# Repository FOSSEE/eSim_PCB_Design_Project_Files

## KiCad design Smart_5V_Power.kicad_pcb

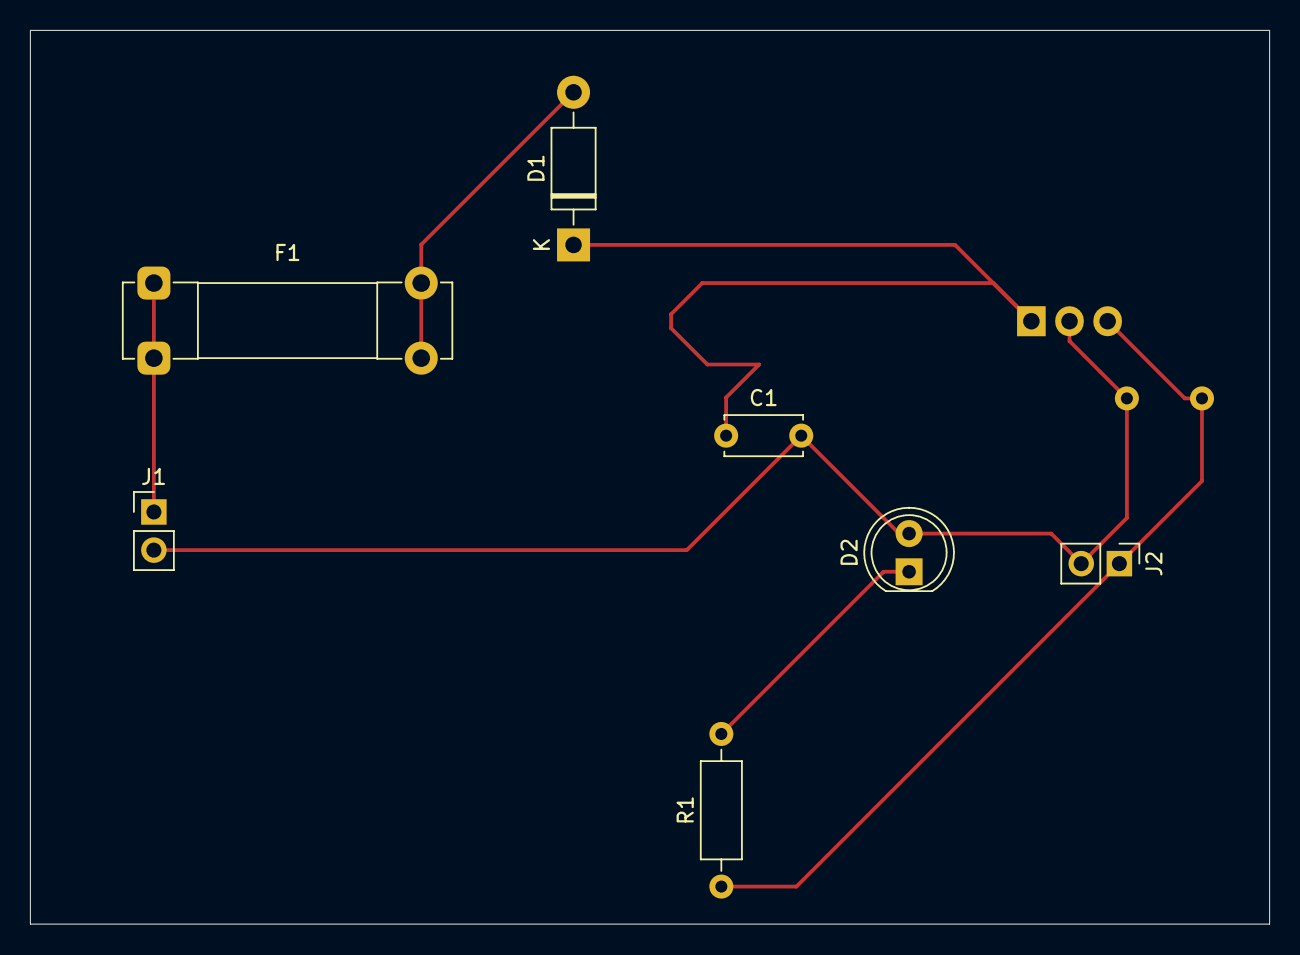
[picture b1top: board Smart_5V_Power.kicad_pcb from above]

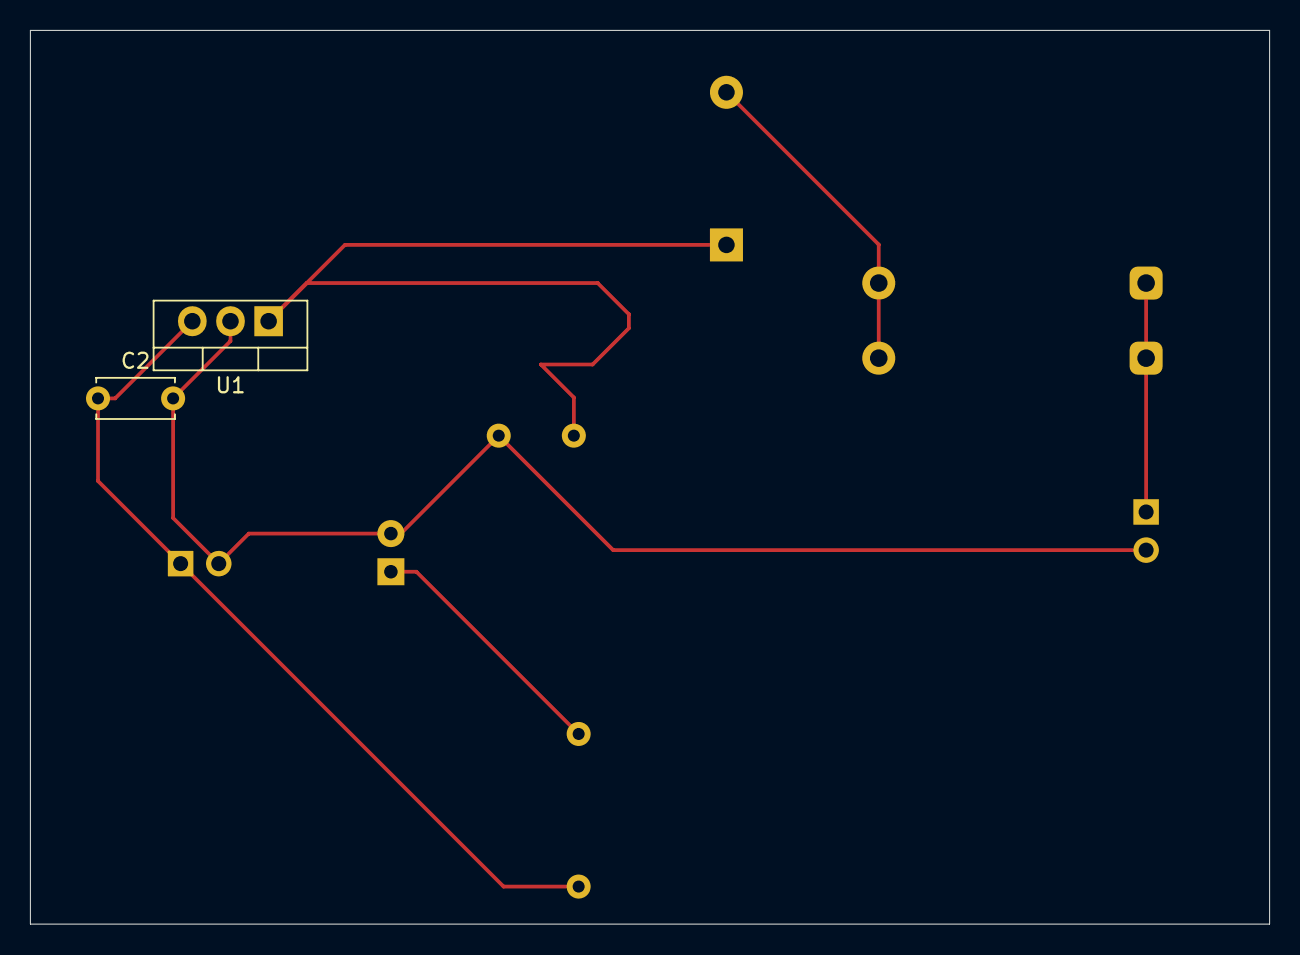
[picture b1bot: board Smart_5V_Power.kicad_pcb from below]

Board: 2 copper layers, 82.5 x 59.5 mm, 9 parts (2 on the bottom side), 6 nets.

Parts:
C1: 0.33uF; C_Disc_D5.0mm_W2.5mm_P5.00mm
C2: 0.1uF; C_Disc_D5.0mm_W2.5mm_P5.00mm
D1: D; D_DO-41_SOD81_P10.16mm_Horizontal
D2: LED; LED_D5.0mm
F1: Fuse; Fuseholder_Clip-5x20mm_Bel_FC-203-22_Lateral_P17.80x5.00mm_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
J1, J2: Conn_01x02; PinHeader_1x02_P2.54mm_Vertical
R1: 1kΩ; R_Axial_DIN0207_L6.3mm_D2.5mm_P10.16mm_Horizontal
U1: L7805; TO-220-3_Vertical

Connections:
GND: C1.2, C2.2, D2.2 (A), J1.2, J2.2, U1.2 (GND)
unnamed: C1.1, D1.1 (K), U1.1 (IN)
unnamed: C2.1, J2.1, R1.1, U1.3 (OUT)
unnamed: D1.2 (A), F1.2
unnamed: D2.1 (K), R1.2
unnamed: F1.1, J1.1

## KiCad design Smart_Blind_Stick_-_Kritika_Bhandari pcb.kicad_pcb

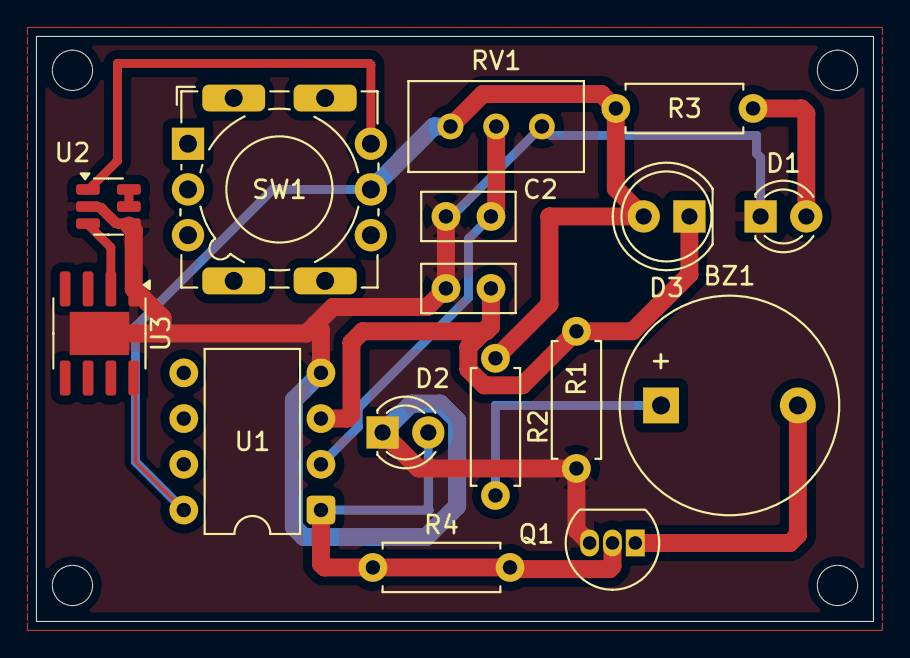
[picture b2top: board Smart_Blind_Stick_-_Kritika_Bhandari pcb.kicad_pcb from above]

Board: 2 copper layers, 46.5 x 32.5 mm, 16 parts (0 on the bottom side), 11 nets.

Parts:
BZ1: Buzzer; Buzzer_12x9.5RM7.6
C1, C2: 10nF; C_Disc_D5.0mm_W2.5mm_P2.50mm
D1, D2: IR204A; LED_D3.0mm_IRBlack
D3: D_Photo; LED_D5.0mm
Q1: BC547; TO-92_Inline
R1, R2: 10k; R_Axial_DIN0207_L6.3mm_D2.5mm_P7.62mm_Horizontal
R3: 220; R_Axial_DIN0207_L6.3mm_D2.5mm_P7.62mm_Horizontal
R4: 1k; R_Axial_DIN0207_L6.3mm_D2.5mm_P7.62mm_Horizontal
RV1: 10k; Potentiometer_Bourns_3296W_Vertical
SW1: SW_SP3T_NR01103; SW_NKK_NR01
U1: LM4250; DIP-8_W7.62mm
U2: TP4057; TSOT-23-6
U3: LGS5500EP; SOIC-8-1EP_3.9x4.9mm_P1.27mm_EP2.41x3.3mm

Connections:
GND: C1.1, C2.1, D1.1 (K), D2.1 (K), Q1.3 (E), R1.2, RV1.1, U1.4 (V-), U2.2 (GND), U2.4 (V_{CC}), U3.1 (ISET), U3.9 (GND)
unnamed: BZ1.1 (+), R2.2
unnamed: BZ1.2 (-), Q1.1 (C)
unnamed: D1.2 (A), R3.1
unnamed: D2.2 (A), Q1.2 (B), R4.1, R4.2, U1.1 (NULL)
unnamed: C1.2, D3.1 (K), R1.1, U1.3 (+)
unnamed: C2.2, RV1.2, U1.2 (-)
unnamed: U2.3 (BAT), U3.2 (VIN)
unnamed: SW1.2, U2.1 (~CHRG)
VCC: D3.2 (A), R2.1, R3.2, RV1.3, SW1.3, U1.8 (IQ), U3.8 (NTC)
out: U2.5 (STDBY), U2.6 (PROG)

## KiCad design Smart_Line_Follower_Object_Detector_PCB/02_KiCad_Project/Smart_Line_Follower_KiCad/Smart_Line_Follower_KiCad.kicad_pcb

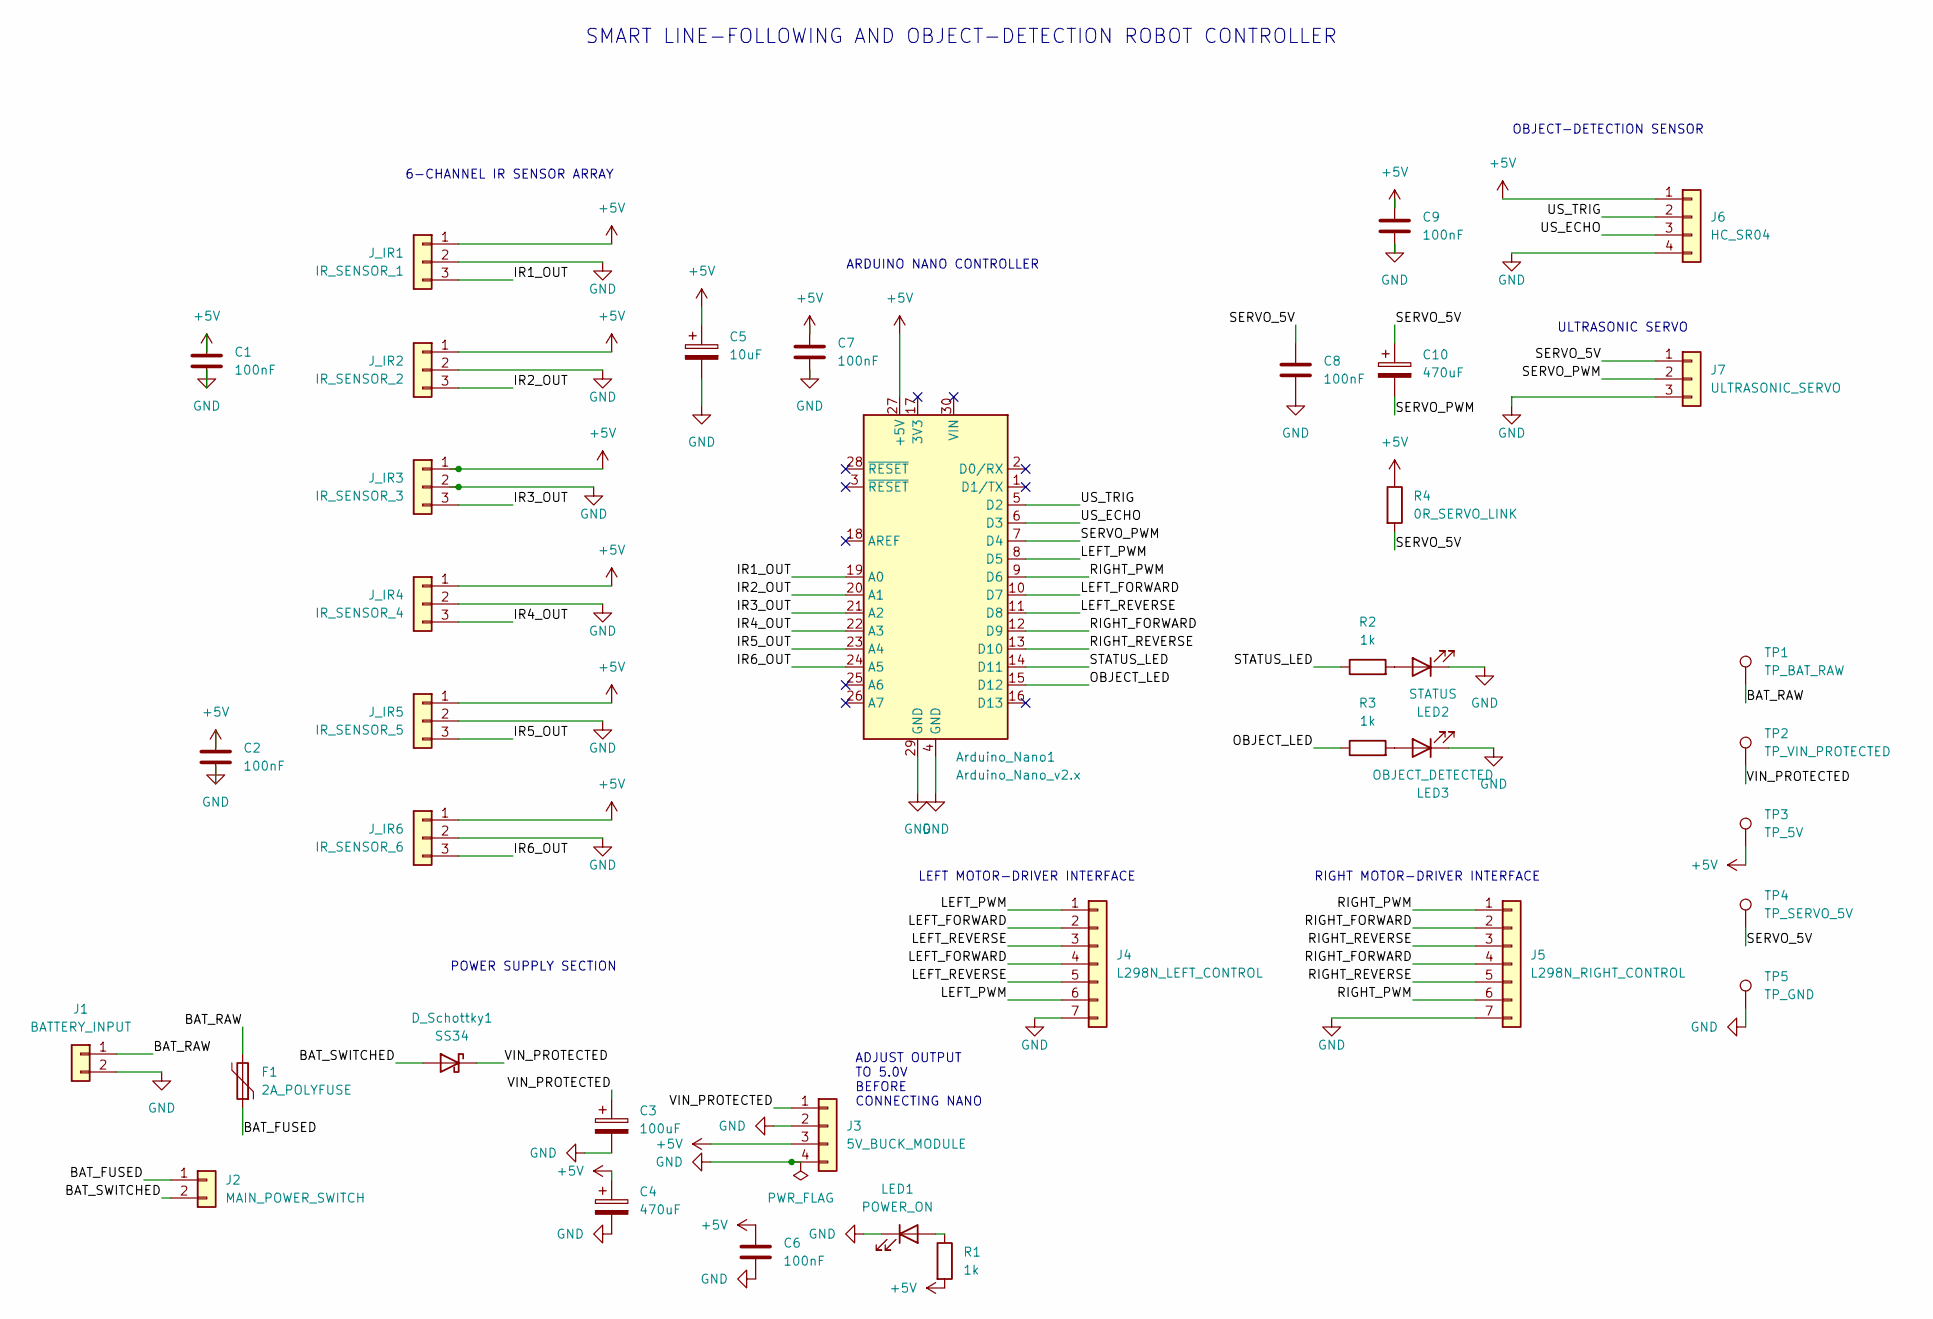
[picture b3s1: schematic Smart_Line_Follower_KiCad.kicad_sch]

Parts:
Arduino_Nano1: Arduino_Nano_v2.x; Arduino_Nano
C1, C2, C6, C7, C8, C9: 100nF; C_Disc_D5.0mm_W2.5mm_P5.00mm
C3: 100uF; CP_Radial_D6.3mm_P2.50mm
C4, C10: 470uF; CP_Radial_D10.0mm_P5.00mm
C5: 10uF; CP_Radial_D5.0mm_P2.00mm
D_Schottky1: SS34; D_SMA
F1: 2A_POLYFUSE; Fuse_Bourns_MF-RG300
J1: BATTERY_INPUT; TerminalBlock_bornier-2_P5.08mm
J2: MAIN_POWER_SWITCH; PinHeader_1x02_P2.54mm_Vertical
J3: 5V_BUCK_MODULE; PinHeader_1x04_P2.54mm_Vertical
J4: L298N_LEFT_CONTROL; PinHeader_1x07_P2.54mm_Vertical
J5: L298N_RIGHT_CONTROL; PinHeader_1x07_P2.54mm_Vertical
J6: HC_SR04; PinHeader_1x04_P2.54mm_Vertical
J7: ULTRASONIC_SERVO; PinHeader_1x03_P2.54mm_Vertical
J_IR1: IR_SENSOR_1; PinHeader_1x03_P2.54mm_Vertical
J_IR2: IR_SENSOR_2; PinHeader_1x03_P2.54mm_Vertical
J_IR3: IR_SENSOR_3; PinHeader_1x03_P2.54mm_Vertical
J_IR4: IR_SENSOR_4; PinHeader_1x03_P2.54mm_Vertical
J_IR5: IR_SENSOR_5; PinHeader_1x03_P2.54mm_Vertical
J_IR6: IR_SENSOR_6; PinHeader_1x03_P2.54mm_Vertical
LED1: POWER_ON; LED_D5.0mm
LED2: STATUS; LED_D5.0mm
LED3: OBJECT_DETECTED; LED_D5.0mm
R1, R2, R3: 1k; R_Axial_DIN0207_L6.3mm_D2.5mm_P10.16mm_Horizontal
R4: 0R_SERVO_LINK; R_Axial_DIN0207_L6.3mm_D2.5mm_P10.16mm_Horizontal
TP1: TP_BAT_RAW; TestPoint_THTPad_D2.0mm_Drill1.0mm
TP2: TP_VIN_PROTECTED; TestPoint_THTPad_D2.0mm_Drill1.0mm
TP3: TP_5V; TestPoint_THTPad_D2.0mm_Drill1.0mm
TP4: TP_SERVO_5V; TestPoint_THTPad_D2.0mm_Drill1.0mm
TP5: TP_GND; TestPoint_THTPad_D2.0mm_Drill1.0mm

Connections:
+5V: Arduino_Nano1.27 (+5V), C1.1, C2.1, C4.1, C5.1, C6.1, C7.1, C9.1, J3.3, J6.1, J_IR1.1, J_IR2.1, J_IR3.1, J_IR4.1, J_IR5.1, J_IR6.1, R1.2, R4.1, TP3.1
/BAT_FUSED: F1.1, J2.1
/BAT_RAW: F1.2, J1.1, TP1.1
/BAT_SWITCHED: D_Schottky1.2 (A), J2.2
/IR1_OUT: Arduino_Nano1.19 (A0), J_IR1.3
/IR2_OUT: Arduino_Nano1.20 (A1), J_IR2.3
/IR3_OUT: Arduino_Nano1.21 (A2), J_IR3.3
/IR4_OUT: Arduino_Nano1.22 (A3), J_IR4.3
/IR5_OUT: Arduino_Nano1.23 (A4), J_IR5.3
/IR6_OUT: Arduino_Nano1.24 (A5), J_IR6.3
/LEFT_FORWARD: Arduino_Nano1.10 (D7), J4.2, J4.4
/LEFT_PWM: Arduino_Nano1.8 (D5), J4.1, J4.6
/LEFT_REVERSE: Arduino_Nano1.11 (D8), J4.3, J4.5
/OBJECT_LED: Arduino_Nano1.15 (D12), R3.1
/RIGHT_FORWARD: Arduino_Nano1.12 (D9), J5.2, J5.4
/RIGHT_PWM: Arduino_Nano1.9 (D6), J5.1, J5.6
/RIGHT_REVERSE: Arduino_Nano1.13 (D10), J5.3, J5.5
/SERVO_5V: C8.1, C10.1, J7.1, R4.2, TP4.1
/SERVO_PWM: Arduino_Nano1.7 (D4), C10.2, J7.2
/STATUS_LED: Arduino_Nano1.14 (D11), R2.1
/US_ECHO: Arduino_Nano1.6 (D3), J6.3
/US_TRIG: Arduino_Nano1.5 (D2), J6.2
/VIN_PROTECTED: C3.1, D_Schottky1.1 (K), J3.1, TP2.1
GND: Arduino_Nano1.4 (GND), Arduino_Nano1.29 (GND), C1.2, C2.2, C3.2, C4.2, C5.2, C6.2, C7.2, C8.2, C9.2, J1.2, J3.2, J3.4, J4.7, J5.7, J6.4, J7.3, J_IR1.2, J_IR2.2, J_IR3.2, J_IR4.2, J_IR5.2, J_IR6.2, LED1.1 (K), LED2.1 (K), LED3.1 (K), TP5.1
unnamed: LED1.2 (A), R1.1
unnamed: LED2.2 (A), R2.2
unnamed: LED3.2 (A), R3.2

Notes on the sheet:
ARDUINO NANO CONTROLLER
LEFT MOTOR-DRIVER INTERFACE
ULTRASONIC SERVO
ADJUST OUTPUT TO 5.0V BEFORE CONNECTING NANO
6-CHANNEL IR SENSOR ARRAY
RIGHT MOTOR-DRIVER INTERFACE
OBJECT-DETECTION SENSOR
SMART LINE-FOLLOWING AND OBJECT-DETECTION ROBOT CONTROLLER
POWER SUPPLY SECTION

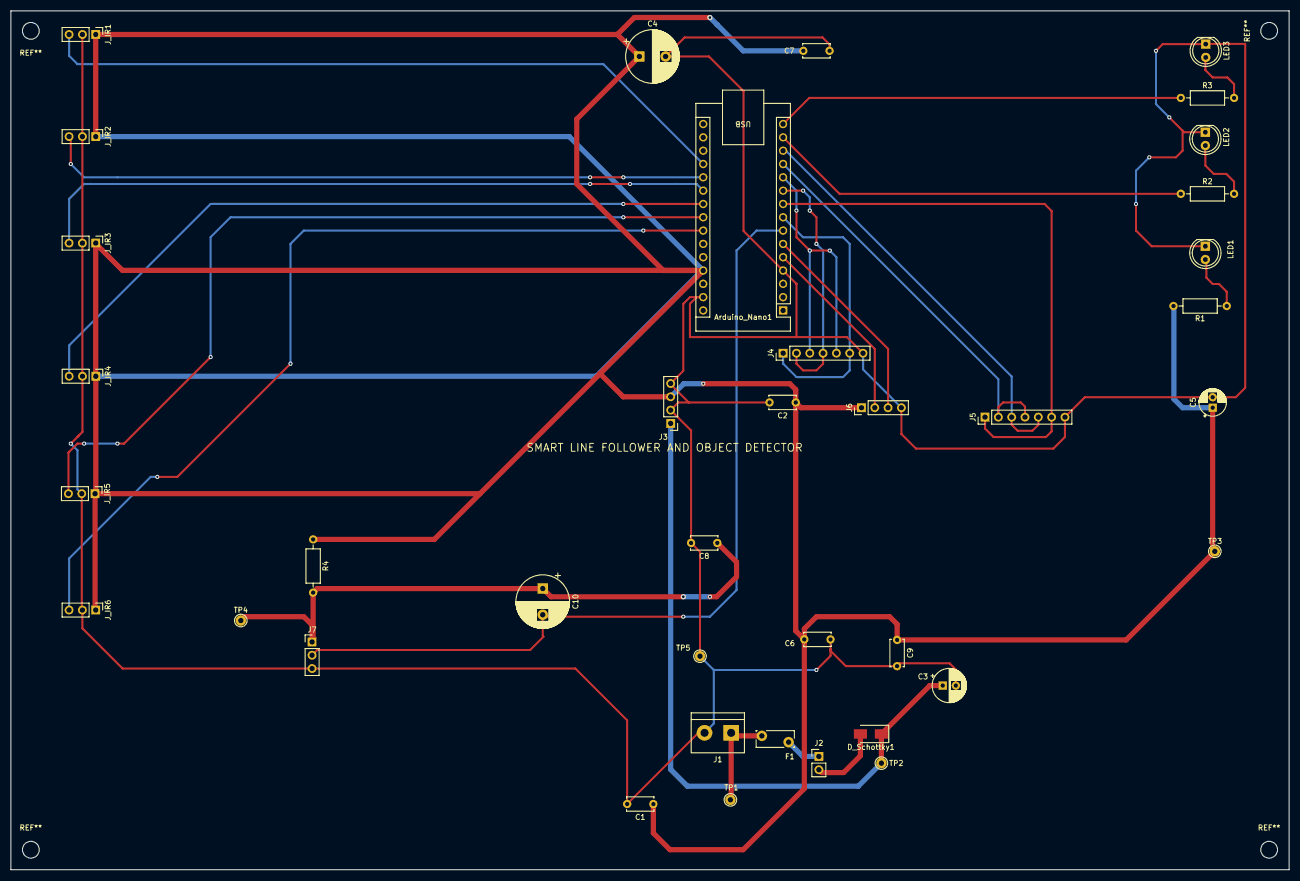
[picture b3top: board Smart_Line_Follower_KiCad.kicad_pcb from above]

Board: 2 copper layers, 243.8 x 163.8 mm, 38 parts (0 on the bottom side), 27 nets.

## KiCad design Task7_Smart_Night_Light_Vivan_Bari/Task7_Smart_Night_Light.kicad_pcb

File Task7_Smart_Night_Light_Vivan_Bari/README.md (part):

# Smart Automatic Night Light Controller Using eSim

### FOSSEE Winter Internship 2026 | Screening Task 7 — PCB Design

Developed by: Vivan Bari  
Domain: Electronics and Communication Engineering  
Software: eSim 2.6, KiCad 9.0.3  
Project Type: Two-Layer PCB Design  
Power Supply: 5V DC

---

## 1. Project Overview

This project presents the schematic design and two-layer PCB layout of a Smart Automatic Night Light Controller using eSim.

The circuit is designed to detect changes in ambient light intensity and automatically control an LED. It uses a Light Dependent Resistor (LDR) as the sensing element, an LM393 comparator for threshold detection, and a 2N7000 N-channel MOSFET for LED switching.

A 10 kΩ potentiometer provides an adjustable reference voltage, allowing the switching threshold to be changed according to the required lighting conditions.

The project was developed as part of Screening Task 7 for the FOSSEE Winter Internship 2026.

The main focus was to complete the PCB design workflow, from schematic capture and footprint assignment to routing, design-rule verification, and 3D visualization.

## 2. Project Objectives

The objectives of this project were to:

1. Design a light-sensitive switching circuit using analog electronic components.
2. Implement the circuit schematic using eSim.
3. Select suitable component footprints for PCB implementation.
4. Design a two-layer PCB using KiCad.
5. Route the required electrical connections while maintaining appropriate clearances.
6. Implement a copper ground plane.
7. Verify the schematic and PCB using ERC and DRC.
8. Generate a 3D representation of the completed PCB.

## 3. Working Principle

The proposed circuit operates by comparing a light-dependent voltage with an adjustable reference voltage.

### 3.1 Light Detection

The light-sensing section consists of an LDR (R1) and a fixed 10 kΩ resistor (R2).

These components form a voltage divider connected between the 5V supply and ground.

The output voltage of this divider depends on the resistance of the LDR.

The sensor voltage is given by:

**V_sensor = 5 × R_LDR / (10,000 + R_LDR)**

where R_LDR represents the instantaneous resistance of the LDR in ohms.

When ambient light intensity increases, the LDR resistance decreases, causing the sensor voltage to fall.

When the surroundings become darker, the LDR resistance increases, causing the sensor voltage to rise.

### 3.2 Voltage Comparison

The LM393 comparator compares the sensor voltage with the reference voltage generated by the 10 kΩ potentiometer (RV1).

The connections are:

- Non-inverting input (+): LDR voltage divider output.
- Inverting input (−): Adjustable potentiometer output.
- Comparator output: MOSFET gate-control circuit.

The LM393 has an open-collector output, so a 10 kΩ pull-up resistor (R4) is connected to the 5V supply.

When the sensor voltage exceeds the reference voltage, the comparator output transistor is switched off, allowing the output voltage to rise through R4.

When the sensor voltage falls below the reference, the comparator pulls its output low.

### 3.3 LED Switching

A 2N7000 N-channel MOSFET acts as the switching device.

Its gate is connected to the LM393 output. The drain is connected to the LED cathode, while the source is connected to ground.

A 330 Ω resistor (R3) limits the LED current.

The intended switching behavior is:

| Lighting condition | Sensor voltage | Comparator output | LED |
|---|---|---|---|
| Bright surroundings | Below reference | LOW | OFF |
| Dark surroundings | Above reference | HIGH through pull-up | ON |

This table describes the intended operation based on the circuit topology. Functional simulation and physical testing have not yet been performed.

## 4. Components Used

The circuit uses the following components:

| Reference | Component | Value / Model | Purpose |
|---|---|---|---|
| U1 | Dual comparator | LM393 | Light-threshold detection |
| R1 | Light Dependent Resistor | R_Photo | Ambient light sensing |
| R2 | Fixed resistor | 10 kΩ | Sensor voltage divider |
| R3 | Fixed resistor | 330 Ω | LED current limiting |
| R4 | Fixed resistor | 10 kΩ | Comparator output pull-up |
| R5 | Fixed resistor | 10 kΩ | Unused comparator bias network |
| R6 | Fixed resistor | 10 kΩ | Unused comparator bias network |
| RV1 | Potentiometer | 10 kΩ | Adjustable threshold |
| Q1 | N-channel MOSFET | 2N7000 | LED switching |
| D1 | LED | LED | Light output |
| C1 | Ceramic capacitor | 100 nF | Supply decoupling |
| J1 | Two-pin connector | 5V input | External power connection |

The LM393 contains two comparators. One comparator is used for light detection, while the second is connected to a defined bias network to avoid floating inputs.

## 5. Schematic Design

The circuit schematic was created using the KiCad Schematic Editor integrated with eSim.

The design was divided into four functional sections:

**Power Supply:** A two-pin connector supplies 5V and GND to the circuit. A 100 nF ceramic capacitor is connected across the supply for decoupling.

**Sensor Circuit:** The LDR and a 10 kΩ fixed resistor form a voltage divider that produces a light-dependent signal.

**Comparator Circuit:** The LM393 compares the sensor voltage against the adjustable reference voltage. A pull-up resistor provides the HIGH output state.

**Output Circuit:** The 2N7000 MOSFET controls current through the LED and its series resistor.

After completing the schematic connections, the Electrical Rules Checker was used to identify and resolve electrical-rule violations.

The final ERC run reported zero errors and zero warnings.

## 6. PCB Design and Layout

The PCB was designed using KiCad 9.0.3 through the eSim 2.6 workflow.

### 6.1 Footprint Assignment

Through-hole footprints were selected for the components.

The major footprints include:

| Component | Footprint |
|---|---|
| LM393 | DIP-8, 7.62 mm width |
| Fixed resistors | DIN0207 axial resistor |
| Ceramic capacitor | 5 mm disc capacitor |
| LED | 5 mm through-hole LED |
| 2N7000 | TO-92 Inline |
| LDR | Vertical LDR footprint |
| Potentiometer | Bourns 3296W Vertical |
| Power connector | Phoenix 2-pin, 5 mm pitch |

The footprint assignments were checked against the schematic pin numbers. Physical compatibility with the exact purchased parts should be confirmed before fabrication.

### 6.2 Component Placement

The components were arranged according to their functions and electrical connections.

The power connector was positioned toward one side of the PCB, followed by the sensor network and comparator.

The LED and MOSFET were placed toward the output side, while the potentiometer was positioned where its adjustment screw could be accessed.

The decoupling capacitor was placed near the LM393.

The layout was organized to reduce unnecessary routing distances while keeping sufficient spacing between component footprints.

### 6.3 PCB Routing

The PCB uses two copper layers:

- **F.Cu:** Front copper layer.
- **B.Cu:** Back copper layer.

A nominal signal track width of 0.30 mm was configured during layout.

Most signal and supply connections were routed on the front copper layer.

The back copper layer was used where necessary to complete connections that could not be routed conveniently on the front.

The routing was performed using KiCad's interactive routing tools, which helped maintain the configured electrical clearances.

### 6.4 Ground Plane

A copper-filled zone connected to the GND net was added on the back copper layer.

The ground plane provides a common ground connection for the circuit components and reduces the need for individual ground traces.

Thermal relief connections were used for through-hole pads where applicable.

The copper zone was refilled before running the final PCB verification.

## 7. Design Verification

The design was checked using KiCad's Electrical Rules Checker and Design Rules Checker.

### 7.1 Electrical Rules Check

The schematic was checked for electrical connection problems and incompatible pin connections.

**Final ERC result:**

| Parameter | Result |
|---|---|
| Errors | 0 |
| Warnings | 0 |

### 7.2 Design Rules Check

The completed PCB was checked for routing violations, disconnected electrical nets, and schematic-to-PCB consistency.

**Final DRC result:**

| Parameter | Result |
|---|---|
| Design-rule violations | 0 |
| Unconnected items | 0 |
| Schematic parity errors | 0 |
| Reported errors | 0 |
| Reported warnings | 0 |

The verification was performed using the configured KiCad design rules.

Five tests were listed as ignored in the DRC window. Therefore, these results should not be interpreted as a complete manufacturing certification.

### 7.3 3D Visualization

The completed PCB was examined using the KiCad 3D Viewer.

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
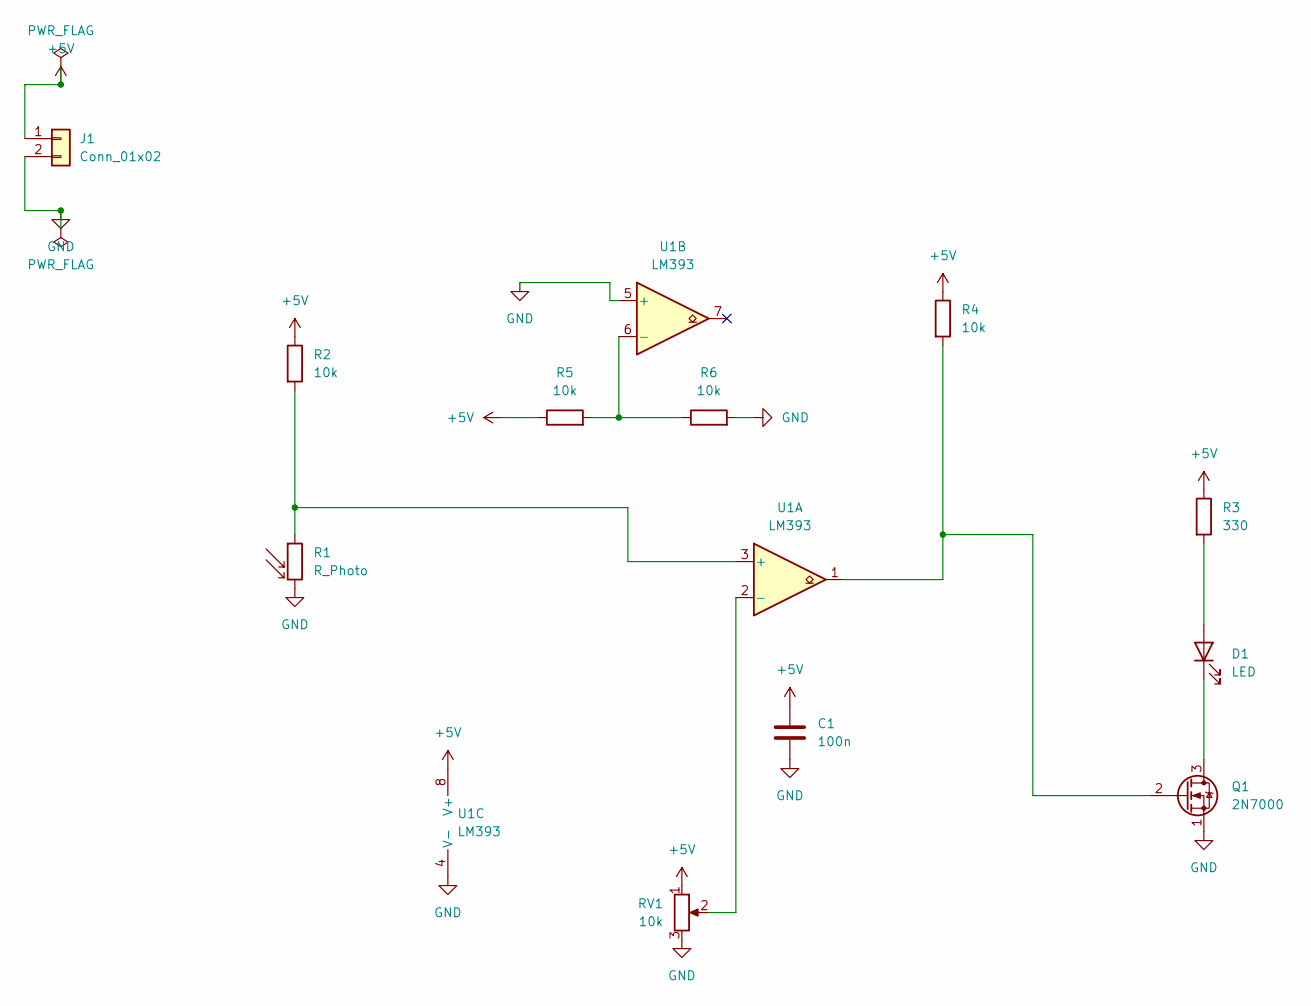
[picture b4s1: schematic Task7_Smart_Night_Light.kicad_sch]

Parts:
C1: 100n; C_Disc_D5.0mm_W2.5mm_P5.00mm
D1: LED; LED_D5.0mm
J1: Conn_01x02; TerminalBlock_Phoenix_MKDS-1,5-2_1x02_P5.00mm_Horizontal
Q1: 2N7000; TO-92_Inline
R1: R_Photo; R_LDR_5.1x4.3mm_P3.4mm_Vertical
R2, R4, R5, R6: 10k; R_Axial_DIN0207_L6.3mm_D2.5mm_P7.62mm_Horizontal
R3: 330; R_Axial_DIN0207_L6.3mm_D2.5mm_P7.62mm_Horizontal
RV1: 10k; Potentiometer_Bourns_3296W_Vertical
U1: LM393; DIP-8_W7.62mm

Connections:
+5V: C1.1, J1.1, R2.1, R3.1, R4.1, R5.1, RV1.1, U1.8 (V+)
GND: C1.2, J1.2, Q1.1 (S), R1.2, R6.2, RV1.3, U1.4 (V-), U1.5 (+)
unnamed: D1.2 (A), R3.2
unnamed: D1.1 (K), Q1.3 (D)
unnamed: Q1.2 (G), R4.2, U1.1
unnamed: R1.1, R2.2, U1.3 (+)
unnamed: RV1.2, U1.2 (-)
unnamed: R5.2, R6.1, U1.6 (-)

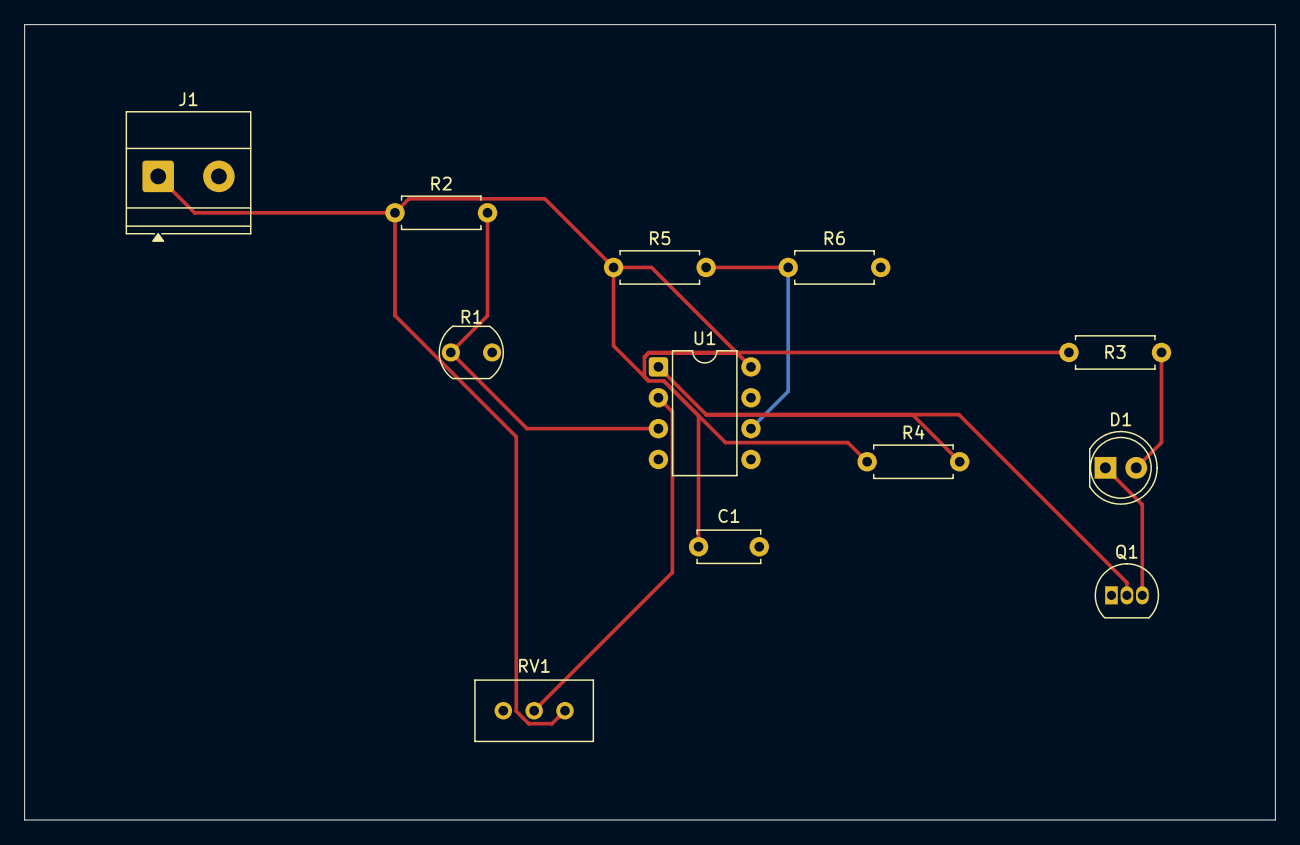
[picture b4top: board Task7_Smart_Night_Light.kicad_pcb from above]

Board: 2 copper layers, 103.0 x 65.5 mm, 12 parts (0 on the bottom side), 8 nets.

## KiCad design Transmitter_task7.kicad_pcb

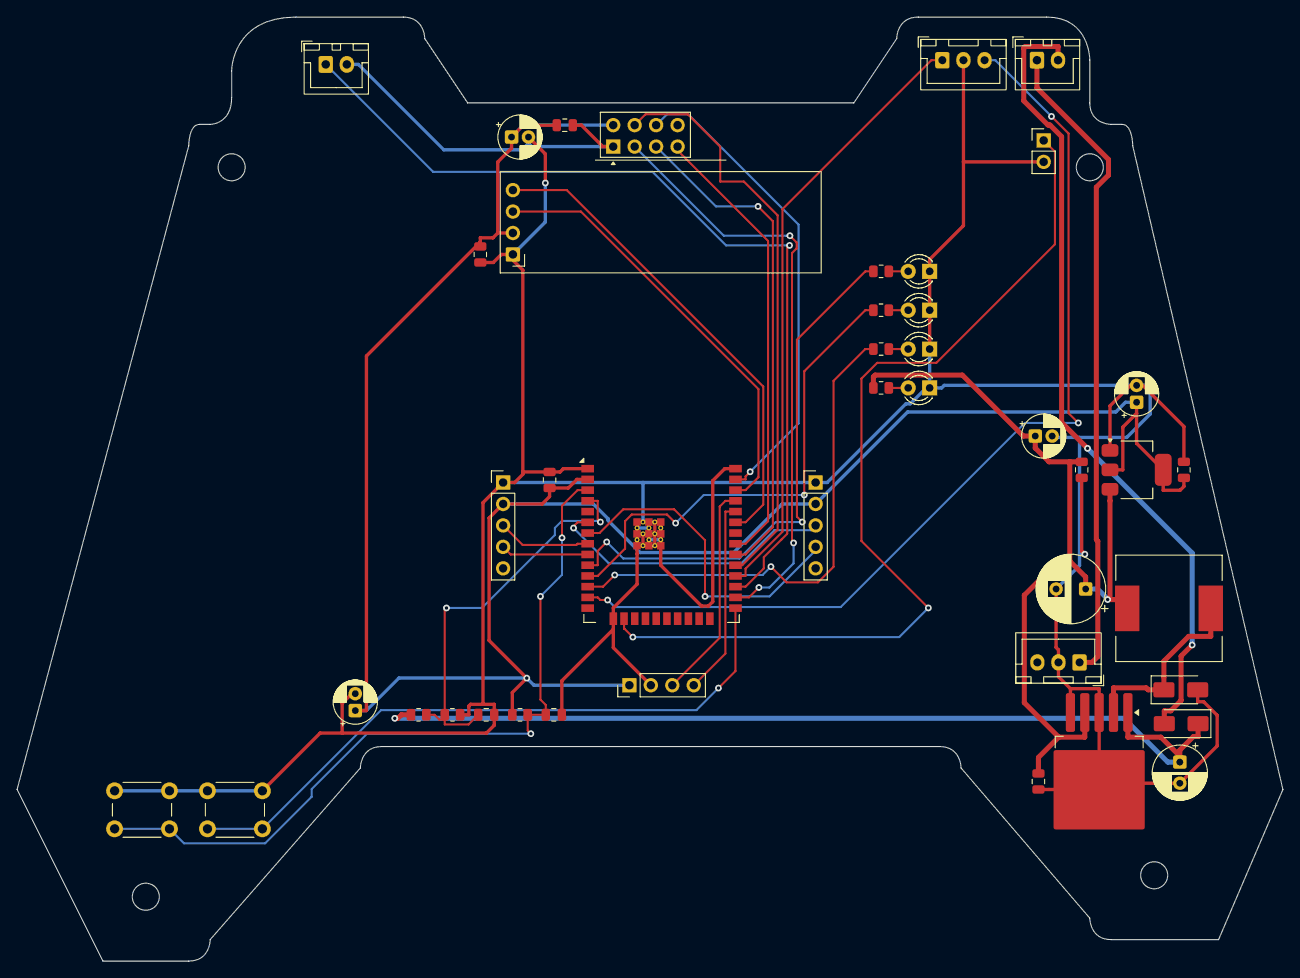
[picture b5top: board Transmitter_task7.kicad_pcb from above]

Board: 2 copper layers, 149.9 x 111.8 mm, 47 parts (0 on the bottom side), 34 nets.

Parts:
C2: 100uF; CP_Radial_D6.3mm_P2.50mm
C3: 220uF; CP_Radial_D8.0mm_P3.50mm
C4, C6, C8, C10, C14, C15: 0.1uF; C_0805_2012Metric
C5, C7, C9, C13: 10uF; CP_Radial_D5.0mm_P2.00mm
C11, C12: 1uF; C_0805_2012Metric
D1, D4, D5, D6: LED; LED_D3.0mm
D2: D_Schottky; D_SMA
D3: SS34; D_SMA
H1, H2, H3, H4: MountingHole; MountingHole_3.2mm_M3
J1: Conn_01x04_Socket; PinHeader_1x04_P2.54mm_Vertical
J2: Conn_01x02_Pin; PinHeader_1x02_P2.54mm_Vertical
J3, J9: Conn_01x05_Socket; PinHeader_1x05_P2.54mm_Vertical
J4: Conn_01x02_Pin; JST_XH_B3B-XH-A_1x03_P2.50mm_Vertical
L1: 33uH; L_12x12mm_H8mm
R1, R2: 10k; R_0805_2012Metric
R3: 20k; R_0805_2012Metric
R4, R5, R6: 330; R_0805_2012Metric
R7: 470; R_0805_2012Metric
SW1, SW3: SW_SPST; JST_XH_B2B-XH-A_1x02_P2.50mm_Vertical
SW2: SW_SPDT; JST_XH_B3B-XH-A_1x03_P2.50mm_Vertical
SW_BOOT1: SW_Push; SW_PUSH_6mm
SW_RST1: SW_Push; SW_PUSH_6mm
U1: NRF24L01_Breakout; nRF24L01_Breakout
U2: ESP32-WROOM-32E
U3: ER_OLEDM0.91_1x-I2C
U5: AMS1117-3.3; SOT-223-3_TabPin2
U6: LM2596S-5; TO-263-5_TabPin3

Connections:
+3V3: C7.1, C8.1, C9.1, C10.1, C13.1, C14.1, C15.1, J1.1, J3.2, J9.2, R1.1, U1.2 (VCC), U2.2 (VDD), U3.2 (VCC), U5.2 (VO)
+5V: C3.1, C4.1, C5.1, C6.1, L1.1, R7.1, U5.3 (VI), U6.4 (FB)
+BATT: C2.1, D2.1 (K), R3.1, U6.1 (VIN)
BATT_SENSE: C12.1, R2.1, R3.2, U2.4 (SENSOR_VP)
BUZZER: J2.1, U2.16 (IO13)
GND: C2.2, C3.2, C4.2, C5.2, C6.2, C7.2, C8.2, C9.2, C10.2, C11.2, C12.2, C13.2, C14.2, C15.2, D1.1 (K), D3.2 (A), D4.1 (K), D5.1 (K), D6.1 (K), J1.2, J2.2, J3.1, J4.2, J9.1, R2.2, SW2.2 (B), SW3.2 (B), SW_BOOT1.1, SW_RST1.1, U1.1 (GND), U2.1 (GND), U2.15 (GND), U2.38 (GND), U2.39 (GND), U3.1 (GND), U5.1 (GND), U6.3 (GND), U6.5 (~ON/OFF)
JOY1_X: J3.3, U2.8 (IO32)
JOY1_Y: J3.4, U2.9 (IO33)
JOY2_X: J9.3, U2.6 (IO34)
JOY2_Y: J9.4, U2.7 (IO35)
LED_ARM: R4.1, U2.10 (IO25)
LED_LINK: R6.1, U2.12 (IO27)
LED_MODE: R5.1, U2.11 (IO26)
NRF_CE: U1.3 (CE), U2.26 (IO4)
NRF_CSN: U1.4 (~CSN), U2.29 (IO5)
NRF_MISO: U1.7 (MISO), U2.31 (IO19)
NRF_MOSI: U1.6 (MOSI), U2.37 (IO23)
NRF_SCK: U1.5 (SCK), U2.30 (IO18)
unnamed: D1.2 (A), R4.2
unnamed: D2.2 (A), SW1.2 (B)
unnamed: D3.1 (K), L1.2, U6.2 (OUT)
unnamed: D4.2 (A), R5.2
unnamed: D5.2 (A), R6.2
unnamed: D6.2 (A), R7.2
unnamed: J4.1, SW1.1 (A)
unnamed: C11.1, R1.2, SW_RST1.2, U2.3 (EN)
unnamed: SW_BOOT1.2, U2.25 (IO0)
OLED_SCL: U2.36 (IO22), U3.3 (SCL)
OLED_SDA: U2.33 (IO21), U3.4 (SDA)
SW_ARM: SW3.1 (A), U2.27 (IO16)
SW_MODE_1: SW2.1 (A), U2.28 (IO17)
SW_MODE_2: SW2.3 (C), U2.13 (IO14)
UART_RX: J1.4, U2.34 (RXD0/IO3)
UART_TX: J1.3, U2.35 (TXD0/IO1)

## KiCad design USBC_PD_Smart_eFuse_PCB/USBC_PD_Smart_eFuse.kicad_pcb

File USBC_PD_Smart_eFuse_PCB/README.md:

# Intelligent USB-C Power Delivery (PD 3.0) Dynamic Sink Trigger and High-Speed Smart eFuse Protection Board

**FOSSEE eSim Semester Long Internship - Autumn 2026 Screening Task 7 Submission**  
**Applicant:** Saibashita Mohanty  
**Architecture:** Advanced 4-Layer High-Current Multilayer PCB (`F.Cu` - `In1.Cu` - `In2.Cu` - `B.Cu`)  
**Toolchain:** eSim 2.5 / KiCad 9.0.3 EDA Suite  
**Verification:** Electrical Rules Check (ERC) Passed | Design Rule Check (DRC) Passed (0 Errors, 0 Warnings, 0 Unconnected)

---

## 📌 1. Project Overview & Objective

This repository contains the complete design and manufacturing files for an **Intelligent USB-C Power Delivery (PD 3.0) Dynamic Sink Trigger and High-Speed Smart eFuse Protection Board**, engineered on an **Advanced 4-Layer Multilayer High-Current Architecture**.

In direct alignment with the FOSSEE Task 7 evaluation criteria stating that *"designs with a higher number of layers may receive additional consideration during the evaluation process"*, this design leverages dedicated internal ground and power planes to achieve superior power delivery, low impedance, electromagnetic shielding, and optimal thermal dissipation.

### Key Specifications:
* **PCB Layer Stackup:** **4 Copper Layers** (Top Signal/Ground, Inner 1 Ground Plane, Inner 2 VBUS Power Plane, Bottom Ground/Signal).
* **Input Interface:** USB Type-C 16-Pin Reversible Receptacle with dual CC line configuration.
* **Negotiable Voltages:** 5V, 9V, 12V, 15V, 20V (selected via 3-bit onboard DIP switch).
* **Maximum Power Handling:** 100W (20V @ 5A continuous).
* **Protection Switch:** AO4407A P-Channel MOSFET (-30V, -12A, $R_{DS(on)} \le 11\text{ m}\Omega$).
* **Current Sensing:** 0.05Ω, 2W high-power low-inductance alloy resistor (2512 SMD).
* **Trip Threshold:** Fully adjustable from 0.5A to 4.0A via a multi-turn precision potentiometer.
* **Transient Clamping:** Bidirectional SMBJ20CA TVS diode (clamping up to ±30kV ESD / inductive spikes).
* **Visual Telemetry:** Green LED (Safe/Power Active) & Red LED (Fault/Trip State).

---

## ⚡ 2. 4-Layer Multilayer Stackup Architecture

| Layer Name | Type | Copper Thickness | Dedicated Function & Electrical Description |
| :--- | :--- | :--- | :--- |
| **1. F.Cu (Top)** | Signal / Ground | 1 oz (35 µm) | High-speed signal routing, component solder pads, and stitched copper ground flood. |
| **2. In1.Cu (Inner 1)** | Internal Plane | 1 oz (35 µm) | **Dedicated Continuous Ground Plane (GND):** Minimizes return loop area, eliminates EMI, and provides complete planar shielding. |
| **3. In2.Cu (Inner 2)** | Internal Plane | 1 oz (35 µm) | **Dedicated Continuous Power Plane (VBUS):** Delivers massive 5A continuous current capacity with near-zero DC resistance and minimal voltage drop. |
| **4. B.Cu (Bottom)** | Ground / Signal | 1 oz (35 µm) | Secondary ground reference plane and auxiliary low-frequency telemetry connections. |

---

## 📐 3. Schematic Diagram

Captured in Eeschema (eSim EDA / KiCad). Fully verified with **Electrical Rules Check (ERC): 0 Errors**.

---

## 📋 4. Component Mapping & Bill of Materials (BOM)

All 19 components use standard, IPC-compliant footprints available in default KiCad / eSim libraries:

| Reference | Value | Footprint | Package / Description |
| :--- | :--- | :--- | :--- |
| **J1** | USB-C 16P | `Connector_USB:USB_C_Receptacle_USB2.0_16P` | 16-Pin Reversible Type-C Connector |
| **U1** | CH224K | `Package_SO:ESSOP-10_3.9x4.9mm_P1.00mm` | USB PD Sink Controller IC |
| **SW1** | SW_DIP_x03 | `Button_Switch_SMD:SW_DIP_SPSTx03_Slide_6.7x9.18mm` | 3-Bit Configuration Switch |
| **SMBJ20CA1** | SMBJ20CA | `Diode_SMD:D_SMB` | 20V Bidirectional TVS Diode |
| **AO4407A1** | AO4407A | `Package_SO:SOIC-8_3.9x4.9mm_P1.27mm` | -30V, -12A P-Channel MOSFET |
| **0.05R2W1** | 0.05Ω 2W | `Resistor_SMD:R_2512_6332Metric` | High-Power Current Sense Resistor |
| **U2** | LM393 | `Package_SO:SOIC-8_3.9x4.9mm_P1.27mm` | Dual Precision Comparator IC |
| **10k1** | 10k Trimpot | `Potentiometer_THT:Potentiometer_Bourns_3296W_Vertical` | Multi-turn Precision Potentiometer |
| **J2** | Screw_Term | `TerminalBlock_Phoenix:TerminalBlock_Phoenix_MKDS-1,5-2-5.08` | 2-Pin 5.08mm Terminal Block |
| **10uf35v1** | 10µF 35V | `Capacitor_SMD:C_1206_3216Metric` | Input Bulk Decoupling Capacitor |
| **0.1uf50v1** | 0.1µF 50V | `Capacitor_SMD:C_0805_2012Metric` | High-Frequency Bypass Capacitor |
| **0.1UF1** | 0.1µF | `Capacitor_SMD:C_0805_2012Metric` | CH224K VDD Decoupling Capacitor |
| **5.1k1, R1** | 5.1kΩ | `Resistor_SMD:R_0805_2012Metric` | CC1/CC2 Pull-Down Resistors |
| **R2** | 10kΩ | `Resistor_SMD:R_0805_2012Metric` | MOSFET Gate Pull-Up Resistor |
| **220R1, 220R2**| 220Ω | `Resistor_SMD:R_0805_2012Metric` | LED Current Limiting Resistors |
| **GreenLED1** | Green LED | `LED_SMD:LED_0805_2012Metric` | Power Output Active Indicator |
| **RedLED1** | Red LED | `LED_SMD:LED_0805_2012Metric` | Fault / Overcurrent Trip Indicator |

---

## 🛠️ 5. PCB Layout & Routing Methodology

---

## ✅ 6. Design Rule Check (DRC) Results (4-Layer Verified)

Verified using KiCad / eSim Design Rules Checker across all 4 copper layers.

```
** Drc report for USBC_PD_Smart_eFuse_PCB.kicad_pcb **
** Created on 2026-11-21T19:12:11+0530 **

** Found 0 DRC violations **

** Found 0 unconnected pads **

** Found 0 Footprint errors **

** End of Report **
```

**Result:** **0 Violations | 0 Unconnected Items | 0 Warnings** (100% Clean).

---

## 🎨 7. 3D Mechanical Demonstration

### 3D Top-Down View

### 3D Isometric View

---

## 📂 8. Project Files Structure

```
USBC_PD_Smart_eFuse_PCB/
├── USBC_PD_Smart_eFuse.kicad_sch          # Main Schematic file
├── USBC_PD_Smart_eFuse.kicad_pcb          # Fully routed 4-layer PCB file (308 KB)
├── USBC_PD_Smart_eFuse.kicad_pro          # KiCad / eSim project configuration
├── USBC_PD_Smart_eFuse.kicad_prl          # Project display settings
├── USBC_PD_Smart_eFuse.net                # Generated Netlist file
├── DRC.rpt                                # Official 4-layer DRC report (0 errors)
├── ERC.rpt                                # Official ERC report
├── Project_Report_Task7_USBC_PD_Smart_eFuse.pdf  # Full 9-Section 4-Layer PDF Report
├── README.md                              # 4-Layer Technical documentation
└── [Images & Renders]                     # High-resolution screenshots and 3D renders
```

---

## 👨‍💻 Submission Details
* **FOSSEE Screening Task:** Task 7 (PCB Design using eSim)
* **Official Repository Fork:** [Saibashita/eSim_PCB_Design_Project_Files](https://github.com/Saibashita/eSim_PCB_Design_Project_Files)
* **Official Pull Request:** [#52](https://github.com/FOSSEE/eSim_PCB_Design_Project_Files/pull/52)
* **Evaluators Invited:** `@Eyantra698Sumanto` and `@OfficialVarad`

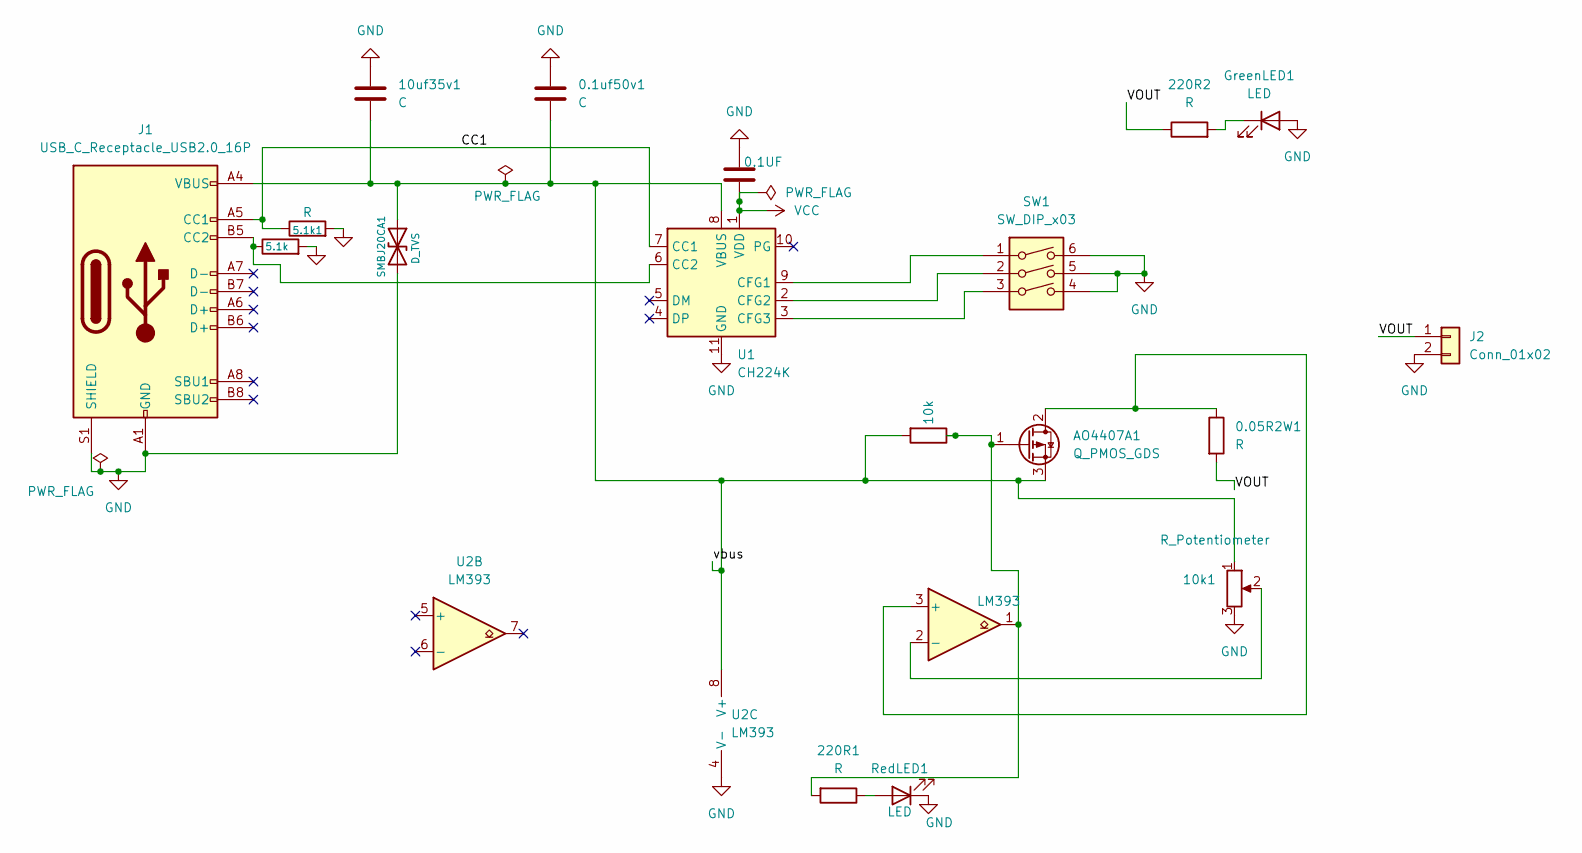
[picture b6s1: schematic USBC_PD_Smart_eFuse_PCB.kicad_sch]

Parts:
0.1UF1: 0.1UF; C_0805_2012Metric
0.1uf50v1: C; C_0805_2012Metric
0.05R2W1: R; R_2512_6332Metric
5.1k1, 220R1, 220R2: R; R_0805_2012Metric
10k1: R_Potentiometer; Potentiometer_Bourns_3296W_Vertical
10uf35v1: C; C_1206_3216Metric
AO4407A1: Q_PMOS_GDS; SOIC-8_3.9x4.9mm_P1.27mm
GreenLED1: LED; LED_0805_2012Metric
J1: USB_C_Receptacle_USB2.0_16P; USB_C_Receptacle_HRO_TYPE-C-31-M-12
J2: Conn_01x02; TerminalBlock_Phoenix_MKDS-1,5-2-5.08_1x02_P5.08mm_Horizont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
R1: 5.1k; R_0805_2012Metric
R2: 10k; R_0805_2012Metric
RedLED1: LED; LED_0805_2012Metric
SMBJ20CA1: D_TVS; D_SMB
SW1: SW_DIP_x03; SW_DIP_SPSTx03_Slide_6.7x9.18mm_W8.61mm_P2.54mm_LowProfile
U1: CH224K; SSOP-10-1EP_3.9x4.9mm_P1mm_EP2.1x3.3mm
U2: LM393; SOIC-8_3.9x4.9mm_P1.27mm

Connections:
/CC1: 5.1k1.1, J1.A5 (CC1), U1.7 (CC1)
/VOUT: 0.05R2W1.2, 220R2.1, J2.1
/vbus: 0.1uf50v1.2, 10k1.1, 10uf35v1.2, AO4407A1.3 (S), J1.A4 (VBUS), J1.A9 (VBUS), J1.B4 (VBUS), J1.B9 (VBUS), R2.2, SMBJ20CA1.1 (A1), U1.8 (VBUS), U2.8 (V+)
GND: 0.1UF1.1, 0.1uf50v1.1, 5.1k1.2, 10k1.3, 10uf35v1.1, GreenLED1.2 (A), J1.A1 (GND), J1.A12 (GND), J1.B1 (GND), J1.B12 (GND), J1.S1 (SHIELD), J2.2, R1.2, RedLED1.1 (K), SMBJ20CA1.2 (A2), SW1.4, SW1.5, SW1.6, U1.11 (GND), U2.4 (V-)
unnamed: 0.05R2W1.1, AO4407A1.2 (D), U2.3 (+)
unnamed: 220R1.2, AO4407A1.1 (G), R2.1, U2.1
unnamed: 220R2.2, GreenLED1.1 (K)
unnamed: J1.B5 (CC2), R1.1, U1.6 (CC2)
unnamed: 220R1.1, RedLED1.2 (A)
unnamed: SW1.1, U1.9 (CFG1)
unnamed: SW1.2, U1.2 (CFG2)
unnamed: SW1.3, U1.3 (CFG3)
unnamed: 10k1.2, U2.2 (-)
VCC: 0.1UF1.2, U1.1 (VDD)
